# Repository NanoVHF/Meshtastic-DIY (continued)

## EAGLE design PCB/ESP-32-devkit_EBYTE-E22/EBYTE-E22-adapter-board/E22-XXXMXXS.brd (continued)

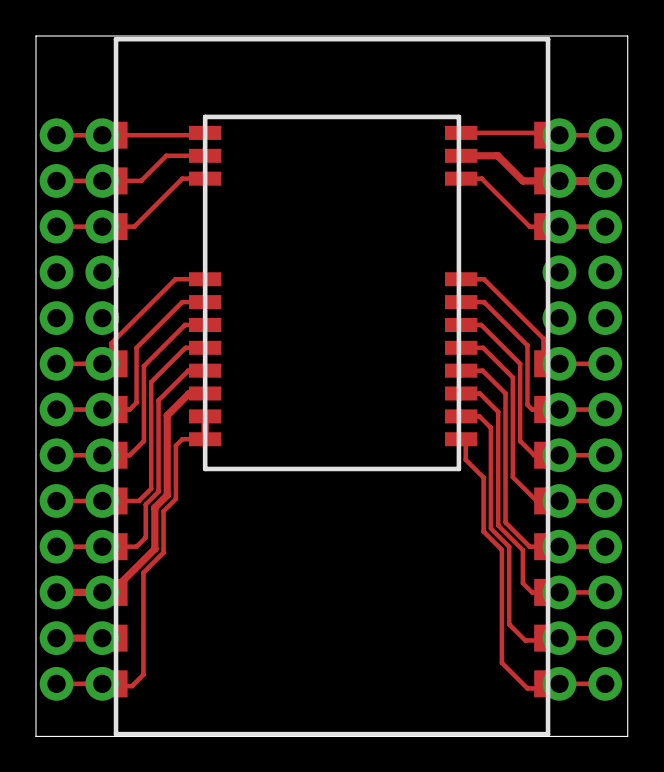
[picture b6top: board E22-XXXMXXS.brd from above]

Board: 2 copper layers, 32.9 x 38.9 mm, 6 parts (0 on the bottom side), 16 nets.

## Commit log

2021-09-09 proposed project structure
2021-09-09 Add shematic
2021-09-09 Create firmware e22-xxxMxxS.bin
    Add file firmware for new shematic
2021-09-09 Add tool software for flashing
2021-09-09 Edit name for firmware
2021-09-09 soldering instruction howto
2021-09-10 typo
2021-09-10 Add schematic E19 modules
2021-09-10 Apd. readme
2021-09-10 Add photos
2021-09-10 test
2021-09-10 First commit, testing
2021-09-10 Update Links.md
    Add links
2021-09-10 Add common links into Links.md
2021-09-10 Update Links.md
    Fix typo
2021-09-11 First version of FAQ_ru.md, scratch
2021-09-11 Add links into Links.md
2021-09-13 Create LoRa_NoNaMe.pdf
    Various simple LoRa modules with aliexpress based on SX1276/1278
2021-09-13 Add NiceRF shematic
2021-09-14 Modify FAQ_ru.md
2021-09-14 Add link into FAQ_ru.md
2021-09-16 Add 3el antenna device
2021-09-16 Add US model
2021-09-17 move files form `doc` to `Docs`
2021-09-27 Add Ebyte TX868-XPL-100 antenna
2021-09-27 Add info into Ebyte_TX868-XPL-100.md
2021-09-27 Add Ebyte TX433-XPL-100 antenna
2021-09-27 Add INNO-868-19WM antenna and data files
2021-09-27 Update README.md
    Fix typo
2021-09-28 Commercial antennas (#8)
    * First commit, testing
    * Update Links.md
    * Update Links.md
    Add links
    * Update Links.md
    * Add common links into Links.md
2021-09-28 Применение МШУ
2021-09-28 Edit FAQ and README
2021-10-08 Fixed bug GPS
    Fixed bug with pin RX GPS.
2021-10-09 Edited Docs/README and Docs/FAQ_ru (#9)
    * First commit, testing
    * Update Links.md
    * Update Links.md
    Add links
    * Update Links.md
    * Add common links into Links.md
2021-12-06 Initial PCB design for ESP32 WROOM-32 & SX1276/RF96 noname modules by Alexey Mikulik
    https://easyeda.com/spgsm/meshtastic-lite
2021-12-14 Initial PCB design for ESP32 WROOM-32 & SX1276/RF96 noname modules by Alexey Mikulik (#10)
    https://easyeda.com/spgsm/meshtastic-lite
2021-12-14 Add 3...8 el yagi
2021-12-21 Add 2nd release
2022-01-04 Upd firmware 1.2.50 for E22-XXXM30S
2022-01-05 Del V2
2022-03-02 Add new V1.1
2022-03-02 Add firmware V1.1.1
2022-05-27 New PCBs design
2022-05-27 Readme & preview
2022-05-29 New PCBs (#11)
    * New PCBs design
    * Readme & preview
2022-05-30 [PCB] Fixed `v1.04-TTGO-T8` & description update
2022-05-30 [PCB] Fixed `v1.04-TTGO-T8` & description update (#12)
2022-06-05 Adapter board for EBYTE E22-XXXM22S E22-XXXM30S
2022-06-05 cropped images
2022-06-05 link to the adapter board
2022-06-05 EBYTE E22 adapter board PCB (#13)
    * Adapter board for EBYTE E22-XXXM22S E22-XXXM30S
    * cropped images
    * link to the adapter board
2022-06-17 `SH1106` and `SSD1306` firmware v1.2.65
2022-07-06 `SH1106` and `SSD1306` firmware v1.2.65 (#14)
2022-07-11 fixes PCB version and description
2022-07-23 Updated revision of the v1.01 PCB
2022-07-23 Fixed drill layout for v.1.05
2022-07-23 Updated EBYTE E22 adapter (removed excessive antenna line)
2022-07-23 Updated PCB v1.03
2022-07-23 Updated PCB v1.02
2022-07-23 Removed untested PCB design
2022-07-23 [PCB] Missing brd&sch for 1.01 & updated 1.02
2022-08-10 v1.04 update
2022-08-10 [PCB] Meshtastic-DIY_v1.06 - TTGO T-Energy T18 V3.0 HAT
2022-08-23 PCB updates (#15)
    * fixes PCB version and description
    * Updated revision of the v1.01 PCB
    * Fixed drill layout for v.1.05
    * Updated EBYTE E22 adapter (removed excessive antenna line)
    * Updated PCB v1.03
    * Updated PCB v1.02
